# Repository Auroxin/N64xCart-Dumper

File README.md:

# N64xCart Dumper

N64xCart Dumper is a source-available hardware / firmware project for dumping Nintendo 64 cartridges as a USB mass storage device. It is based on the excellent DreamDumper64 project and the `DrmDmp64_mass` firmware, with changes for the N64xCart Dumper hardware.

## Project Status

This repository contains:

- `firmware/N64xCartDumper/` - RP2040 firmware adapted for the N64xCart Dumper board.
- `hardware-v2.1/` - current and recommended KiCad and production files.
- `hardware-v1.1/` - legacy hardware files, retained for reference only.
- `extras/` - extra project files, if any.

The device appears to the computer as a USB mass storage device. The virtual FAT16 disk exposes N64 cartridge data and save data files such as ROM, EEPROM, SRAM and FlashRAM where supported by the firmware.

## Origin and Credits

This project exists because of prior open source work. Please visit and support the original authors:

- DreamDumper64 hardware project by khill25: https://github.com/khill25/Dreamdumper
- `DrmDmp64_mass` firmware by nopjne: https://github.com/nopjne/drmdmp64_mass
- Special thanks to [selunders](https://github.com/selunders/N64xCart-Dumper/tree/read_eeprom) for identifying the hardware v1.1 issues affecting CIC information and EEPROM reading, and for providing a detailed repair proposal that helped guide the updated hardware design.
- TinyUSB USB stack: https://github.com/hathach/tinyusb
- Raspberry Pi Pico / RP2040 SDK ecosystem: https://github.com/raspberrypi/pico-sdk

My changes are focused on adapting the firmware and hardware layout for the N64xCart Dumper board, including the PCB layout, production files, and acrylic enclosure design.

## Hardware

The hardware in this repository was redrawn and laid out for the N64xCart Dumper form factor while following the DreamDumper64 hardware principles.

> [!IMPORTANT]
> **Use hardware v2.1 for all new DIY builds. Do not build hardware v1.1.** Version 1.1 does not support reading CIC chip information from N64 cartridges or reading EEPROM save data. Hardware v2.1 resolves these limitations and is expected to be the final hardware revision. The v1.1 files remain in this repository for historical reference only.

<p align="center">
  
  <br>
  <sub><strong>N64xCart Dumper v2.1 — Rear view</strong></sub>
</p>

Current, recommended hardware files:

- KiCad project: `hardware-v2.1/PCB/N64xCartDumper-v2.1.kicad_pro`
- Schematic: `hardware-v2.1/PCB/N64xCartDumper-v2.1.kicad_sch`
- PCB layout: `hardware-v2.1/PCB/N64xCartDumper-v2.1.kicad_pcb`
- Production archive: `hardware-v2.1/production/N64xCart-Dumper-v2.1-20260813.zip`

Legacy v1.1 files are under `hardware-v1.1/` and are not recommended for manufacturing.

## Firmware

The firmware is based on `DrmDmp64_mass`, a mass storage device firmware for DreamDumper64. It has been modified for the N64xCart Dumper hardware.

Important local changes include:

- USB product strings changed to `N64xCart Dumper`.
- Hardware pin and LED configuration adapted for this board.
- Virtual disk label/product information updated for N64xCart Dumper.
- Project files arranged under `firmware/N64xCartDumper/`.

## Building Firmware

The active firmware build entry is the CMake project in `firmware/N64xCartDumper/`.

Typical build flow:

```sh
cd firmware/N64xCartDumper
mkdir build
cd build
cmake ..
cmake --build .
(optional) put pico in bootloader mode and copy the N64xCartDumper.uf2 to the attached drive.
```

You will need a working Raspberry Pi Pico / RP2040 build environment, including the Pico SDK, CMake, a supported ARM GCC toolchain, and the TinyUSB dependencies used by this project.

Note: the included `Makefile` appears to be inherited from an earlier TinyUSB example layout and may not match the current source file names. Prefer the CMake build unless you intentionally update the Makefile.

## Buying a Finished Unit

I also sell assembled N64xCart Dumper units on AliExpress. Units sold through the product link below use the latest v2.1 hardware. Buying one helps support the time spent on PCB layout, testing, assembly, enclosure design, and continued project maintenance.

- Support Us: [Product Link](https://www.aliexpress.com/item/1005012654363194.html)

Thank you for supporting this project. If you build your own non-commercial unit, improve the design, or find a bug, contributions and feedback are welcome.

## License Notes

The original N64xCart Dumper hardware designs, documentation, and project-specific modifications are licensed for **personal and other non-commercial use only** under the terms in [`LICENSE`](LICENSE). Commercial use—including manufacturing or selling boards, assembled units, kits, or derivative products—is prohibited without prior written permission from the applicable copyright holder.

This non-commercial restriction means the project is source-available, but it is not Open Source Hardware or open-source software under the commonly accepted OSI/OSHWA definitions.

This repository also contains code and design work derived from third-party projects. The project-level license does not replace or restrict third-party rights. Check the original projects, file headers, and bundled license files for the terms that apply to those materials:

- `DrmDmp64_mass`: https://github.com/nopjne/drmdmp64_mass
- DreamDumper64: https://github.com/khill25/Dreamdumper
- TinyUSB license file included at `firmware/N64xCartDumper/external/tinyusb/LICENSE`

Source files inherited from `DrmDmp64_mass` include their original copyright notices and headers. Third-party components remain the property of their respective copyright holders and are governed by their respective terms.

## Disclaimer

This is an independent hobbyist/source-available hardware project. It is not affiliated with or endorsed by Nintendo. Use it only with cartridges and data you legally own and are allowed to back up under your local laws.

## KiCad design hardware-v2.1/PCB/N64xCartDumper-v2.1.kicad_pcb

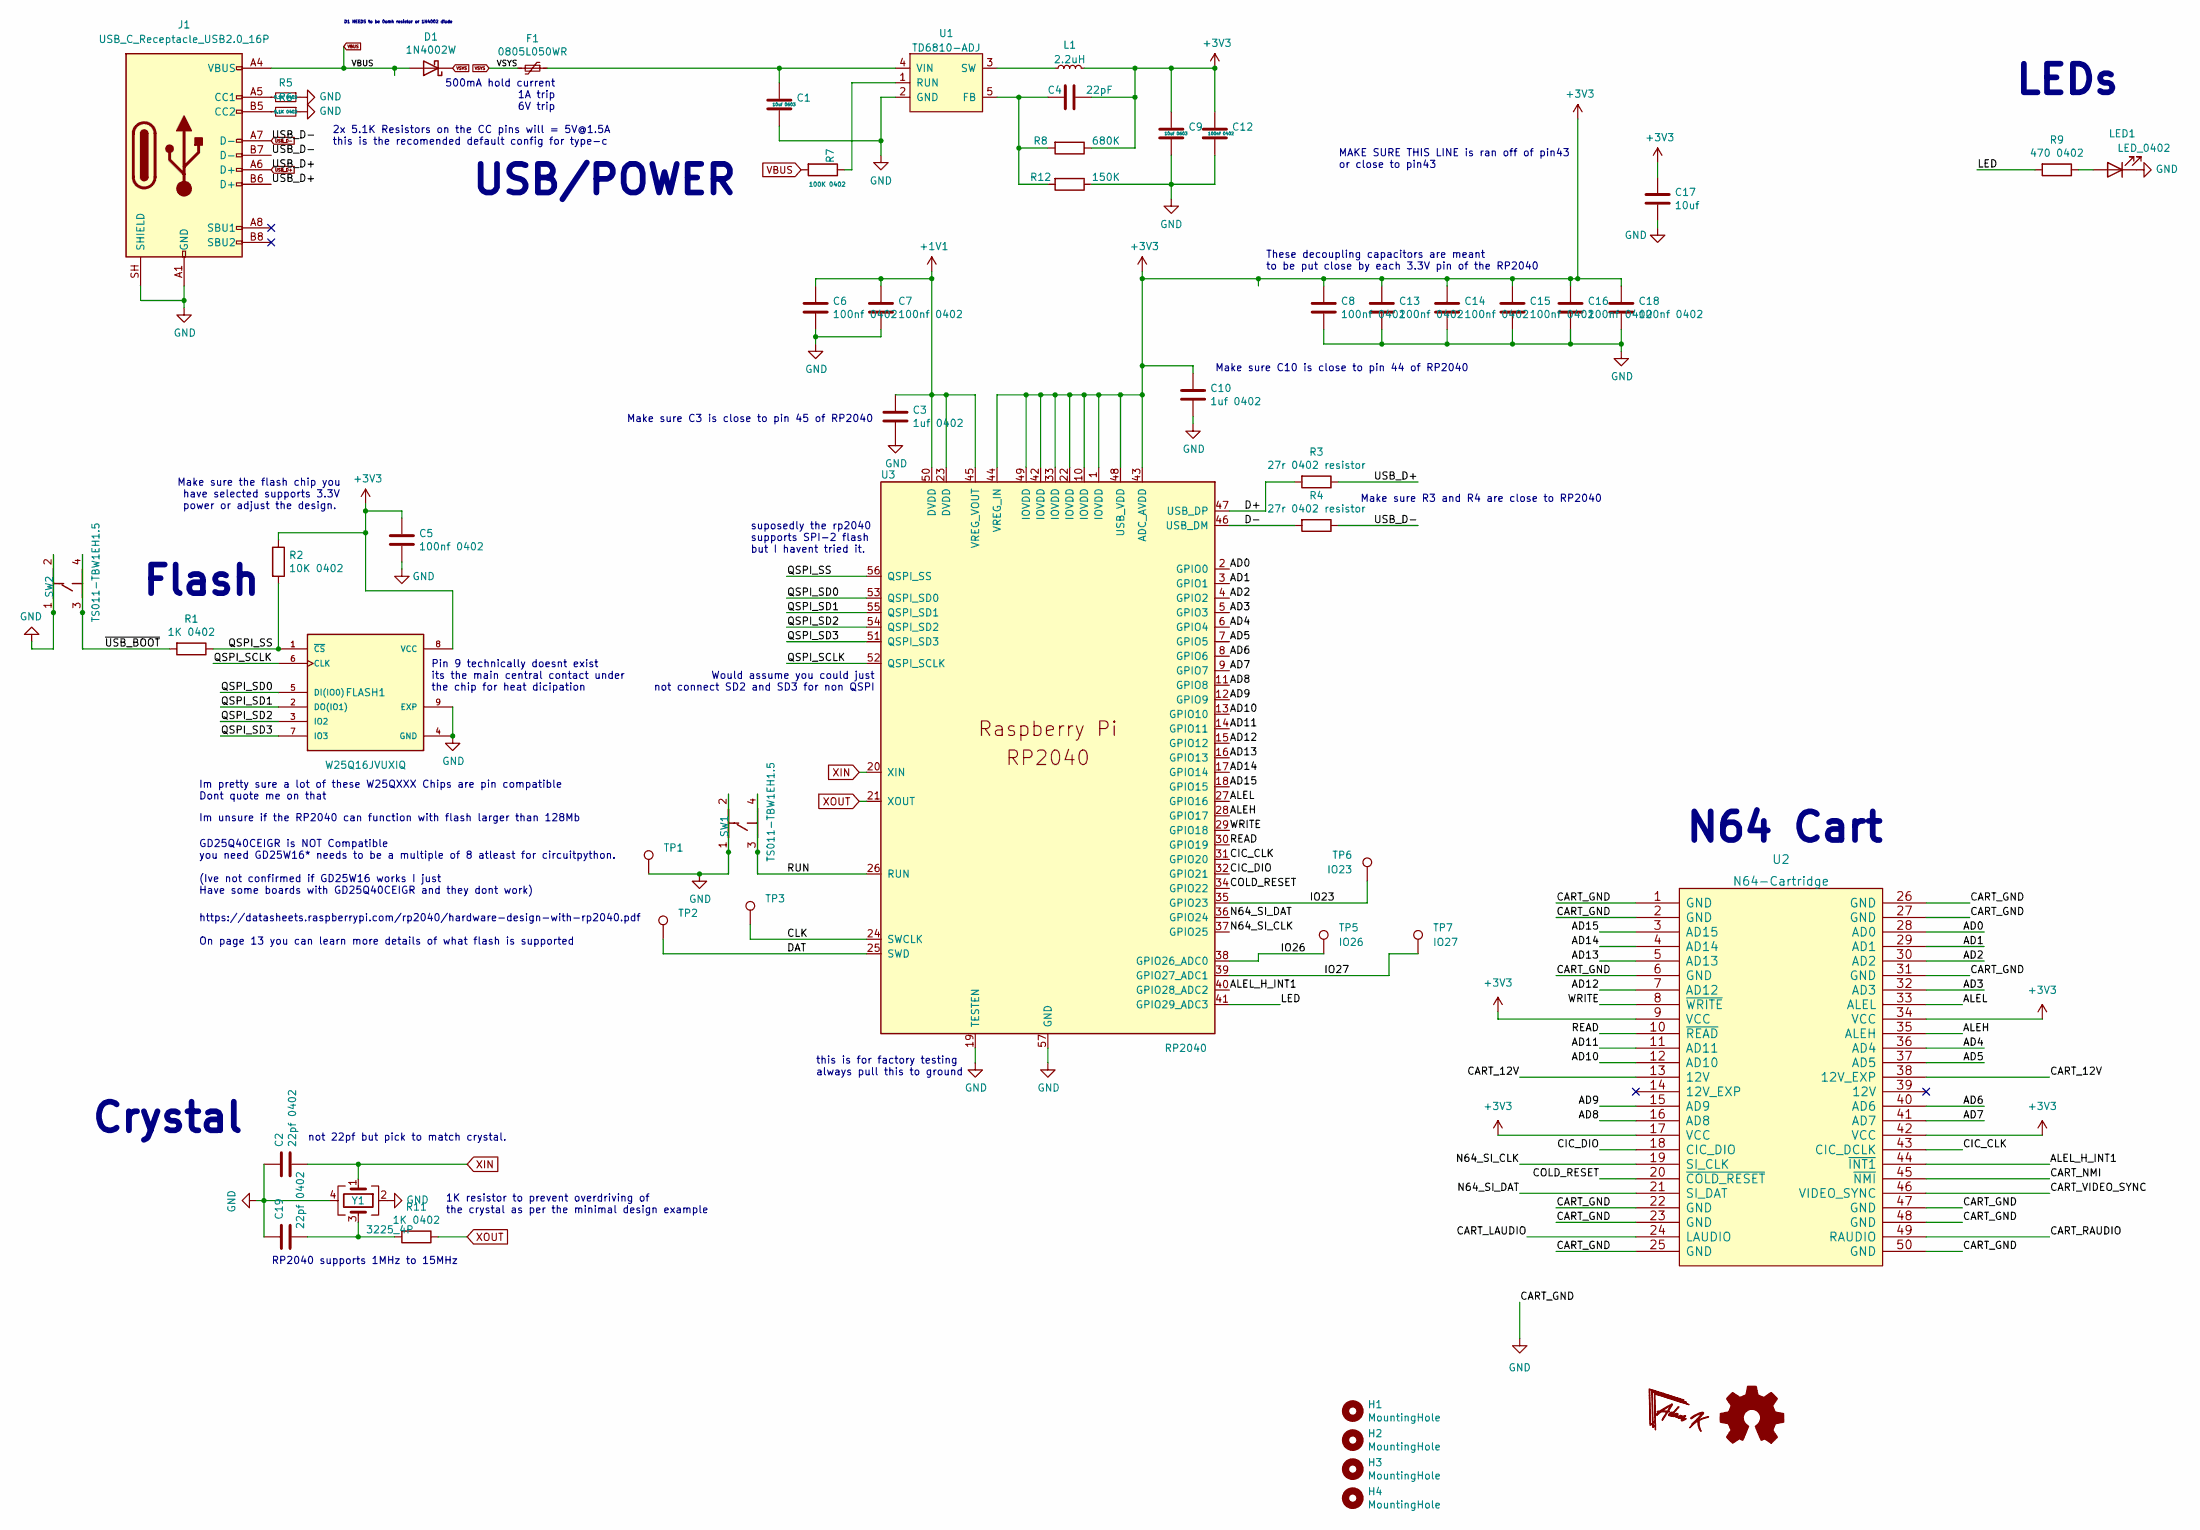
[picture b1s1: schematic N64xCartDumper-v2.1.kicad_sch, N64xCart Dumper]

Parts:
C1, C9: 10uf 0603; C_0603_1608Metric
C2, C19: 22pf 0402; C_0402_1005Metric
C3, C10: 1uf 0402; C_0402_1005Metric
C4: 22pF; C_0402_1005Metric
C5, C6, C7, C8, C12, C13, C14, C15, C16, C18: 100nf 0402; C_0402_1005Metric
C17: 10uf; C_0603_1608Metric
D1: 1N4002W; D_SOD-123
F1: 0805L050WR; Fuse_0805_2012Metric
FLASH1: W25Q16JVUXIQ; Winbond_USON-8-1EP_3x2mm_P0.5mm_EP0.2x1.6mm
H1, H2, H3, H4: MountingHole; MountingHole_3.2mm_M3_Pad
J1: USB_C_Receptacle_USB2.0_16P; USB-C-SMD_SHOU_TYPE-C-16P-CB1.6
L1: 2.2uH; WPN252010UF2R2MT
LED1: LED_0402; LED_0603_1608Metric
R1, R11: 1K 0402; R_0402_1005Metric
R2: 10K 0402; R_0402_1005Metric
R3, R4: 27r 0402 resistor; R_0402_1005Metric
R5, R6: 5.1K 0402; R_0402_1005Metric
R7: 100K 0402; R_0402_1005Metric
R8: 680K; R_0402_1005Metric
R9: 470 0402; R_0402_1005Metric
R12: 150K; R_0402_1005Metric
SW1, SW2: TS011-TBW1EH1.5; SW-SMD_4P-L5.2-W5.2-1; Manufacturer Part TS011-TBW1EH1.5; LCSC Part Name 4*4*1.5mm 立贴 180GF 铜头轻触开关
TP1: GND; TestPoint_Pad_D1.0mm
TP2: DAT; TestPoint_Pad_D1.0mm
TP3: CLK; TestPoint_Pad_D1.0mm
TP5: IO26; TestPoint_Pad_D1.0mm
TP6: IO23; TestPoint_Pad_D1.0mm
TP7: IO27; TestPoint_Pad_D1.0mm
U1: TD6810-ADJ; SOT-23-5
U2: N64-Cartridge; N64-CONN
U3: RP2040; RP2040-QFN-56; LCSC C2040
Y1: 3225_4P; Crystal_SMD_3225-4Pin_3.2x2.5mm

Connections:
+1V1: C3.1, C6.1, C7.1, U3.23 (DVDD), U3.45 (VREG_VOUT), U3.50 (DVDD)
+3V3: C4.2, C5.1, C8.1, C9.1, C10.1, C12.1, C13.1, C14.1, C15.1, C16.1, C17.1, C18.1, FLASH1.8 (VCC), L1.2, R2.1, R8.1, U2.9 (VCC), U2.17 (VCC), U2.34 (VCC), U2.42 (VCC), U3.1 (IOVDD), U3.10 (IOVDD), U3.22 (IOVDD), U3.33 (IOVDD), U3.42 (IOVDD), U3.43 (ADC_AVDD), U3.44 (VREG_IN), U3.48 (USB_VDD), U3.49 (IOVDD)
/AD0: U2.28 (AD0), U3.2 (GPIO0)
/AD1: U2.29 (AD1), U3.3 (GPIO1)
/AD2: U2.30 (AD2), U3.4 (GPIO2)
/AD3: U2.32 (AD3), U3.5 (GPIO3)
/AD4: U2.36 (AD4), U3.6 (GPIO4)
/AD5: U2.37 (AD5), U3.7 (GPIO5)
/AD6: U2.40 (AD6), U3.8 (GPIO6)
/AD7: U2.41 (AD7), U3.9 (GPIO7)
/AD8: U2.16 (AD8), U3.11 (GPIO8)
/AD9: U2.15 (AD9), U3.12 (GPIO9)
/AD10: U2.12 (AD10), U3.13 (GPIO10)
/AD11: U2.11 (AD11), U3.14 (GPIO11)
/AD12: U2.7 (AD12), U3.15 (GPIO12)
/AD13: U2.5 (AD13), U3.16 (GPIO13)
/AD14: U2.4 (AD14), U3.17 (GPIO14)
/AD15: U2.3 (AD15), U3.18 (GPIO15)
/ALEH: U2.35 (ALEH), U3.28 (GPIO17)
/ALEL: U2.33 (ALEL), U3.27 (GPIO16)
/ALEL_H_INT1: U2.44 (~INT1), U3.40 (GPIO28_ADC2)
/CART_12V: U2.13 (12V), U2.38 (12V_EXP)
/CART_LAUDIO: U2.24 (LAUDIO)
/CART_NMI: U2.45 (~NMI)
/CART_RAUDIO: U2.49 (RAUDIO)
/CART_VIDEO_SYNC: U2.46 (VIDEO_SYNC)
/CIC_CLK: U2.43 (CIC_DCLK), U3.31 (GPIO20)
/CIC_DIO: U2.18 (CIC_DIO), U3.32 (GPIO21)
/CLK: TP3.1 (1_1), U3.24 (SWCLK)
/COLD_RESET: U2.20 (~COLD_RESET), U3.34 (GPIO22)
/D+: R3.2, U3.47 (USB_DP)
/D-: R4.2, U3.46 (USB_DM)
/DAT: TP2.1 (1_1), U3.25 (SWD)
/IO23: TP6.1 (1_1), U3.35 (GPIO23)
/IO26: TP5.1 (1_1), U3.38 (GPIO26_ADC0)
/IO27: TP7.1 (1_1), U3.39 (GPIO27_ADC1)
/LED: R9.2, U3.41 (GPIO29_ADC3)
/N64_SI_CLK: U2.19 (SI_CLK), U3.37 (GPIO25)
/N64_SI_DAT: U2.21 (SI_DAT), U3.36 (GPIO24)
/QSPI_SCLK: FLASH1.6 (CLK), U3.52 (QSPI_SCLK)
/QSPI_SD0: FLASH1.5 (DI(IO0)), U3.53 (QSPI_SD0)
/QSPI_SD1: FLASH1.2 (DO(IO1)), U3.55 (QSPI_SD1)
/QSPI_SD2: FLASH1.3 (IO2), U3.54 (QSPI_SD2)
/QSPI_SD3: FLASH1.7 (IO3), U3.51 (QSPI_SD3)
/QSPI_SS: FLASH1.1 (~CS), R1.1, R2.2, U3.56 (QSPI_SS)
/READ: U2.10 (~READ), U3.30 (GPIO19)
/RUN: SW1.3, SW1.4, U3.26 (RUN)
/WRITE: U2.8 (~WRITE), U3.29 (GPIO18)
/~USB_BOOT: R1.2, SW2.3, SW2.4
GND: C1.2, C2.1, C3.2, C5.2, C6.2, C7.2, C8.2, C9.2, C10.2, C12.2, C13.2, C14.2, C15.2, C16.2, C17.2, C18.2, C19.1, FLASH1.4 (GND), FLASH1.9 (EXP), J1.A1 (GND), J1.A12 (GND), J1.B1 (GND), J1.B12 (GND), J1.SH (SHIELD), LED1.1 (K), R5.1, R6.1, R12.1, SW1.1, SW1.2, SW2.1, SW2.2, TP1.1 (1_1), U1.2 (GND), U2.1 (GND), U2.2 (GND), U2.6 (GND), U2.22 (GND), U2.23 (GND), U2.25 (GND), U2.26 (GND), U2.27 (GND), U2.31 (GND), U2.47 (GND), U2.48 (GND), U2.50 (GND), U3.19 (TESTEN), U3.57 (GND), Y1.2, Y1.4
unnamed: C19.2, R11.2, Y1.3
unnamed: J1.A5 (CC1), R5.2
unnamed: J1.B5 (CC2), R6.2
unnamed: LED1.2 (A), R9.1
unnamed: C4.1, R8.2, R12.2, U1.5 (FB)
unnamed: R7.1, U1.1 (RUN)
unnamed: L1.1, U1.3 (SW)
unnamed: C1.1, F1.1, U1.4 (VIN)
USB_D+: J1.A6 (D+), J1.B6 (D+), R3.1
USB_D-: J1.A7 (D-), J1.B7 (D-), R4.1
VBUS: D1.2 (A), J1.A4 (VBUS), J1.A9 (VBUS), J1.B4 (VBUS), J1.B9 (VBUS), R7.2
VSYS: D1.1 (K), F1.2
XIN: C2.2, U3.20 (XIN), Y1.1
XOUT: R11.1, U3.21 (XOUT)

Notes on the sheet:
USB/POWER
GD25Q40CEIGR is NOT Compatible you need GD25W16* needs to be a multiple of 8 atleast for circuitpython. (Ive not confirmed if GD25W16 works I just Have some boards with GD25Q40CEIGR and they dont work)
D1 NEEDS to be 0omh resistor or 1N4002 diode
https://datasheets.raspberrypi.com/rp2040/hardware-design-with-rp2040.pdf On page 13 you can learn more details of what flash is supported
Pin 9 technically doesnt exist its the main central contact under the chip for heat dicipation
Make sure R3 and R4 are close to RP2040
this is for factory testing always pull this to ground
Im unsure if the RP2040 can function with flash larger than 128Mb
Would assume you could just not connect SD2 and SD3 for non QSPI
These decoupling capacitors are meant to be put close by each 3.3V pin of the RP2040
N64 Cart
Flash
Im pretty sure a lot of these W25QXXX Chips are pin compatible Dont quote me on that
not 22pf but pick to match crystal.
2x 5.1K Resistors on the CC pins will = 5V@1.5A this is the recomended default config for type-c
suposedly the rp2040 supports SPI-2 flash but I havent tried it.
1K resistor to prevent overdriving of the crystal as per the minimal design example
LEDs
RP2040 supports 1MHz to 15MHz
Make sure the flash chip you have selected supports 3.3V power or adjust the design.
MAKE SURE THIS LINE is ran off of pin43 or close to pin43
Crystal
500mA hold current 1A trip 6V trip
Make sure C3 is close to pin 45 of RP2040
Make sure C10 is close to pin 44 of RP2040

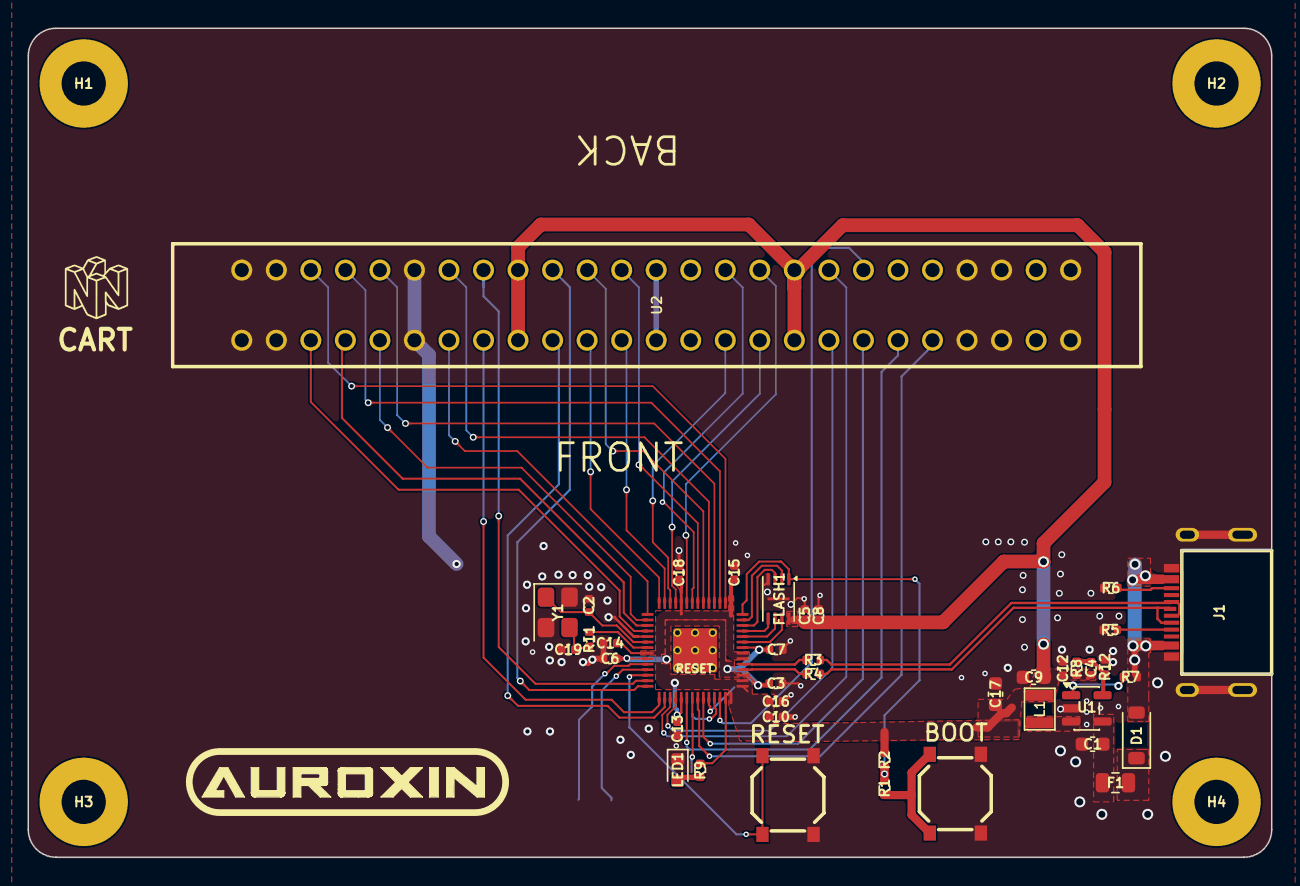
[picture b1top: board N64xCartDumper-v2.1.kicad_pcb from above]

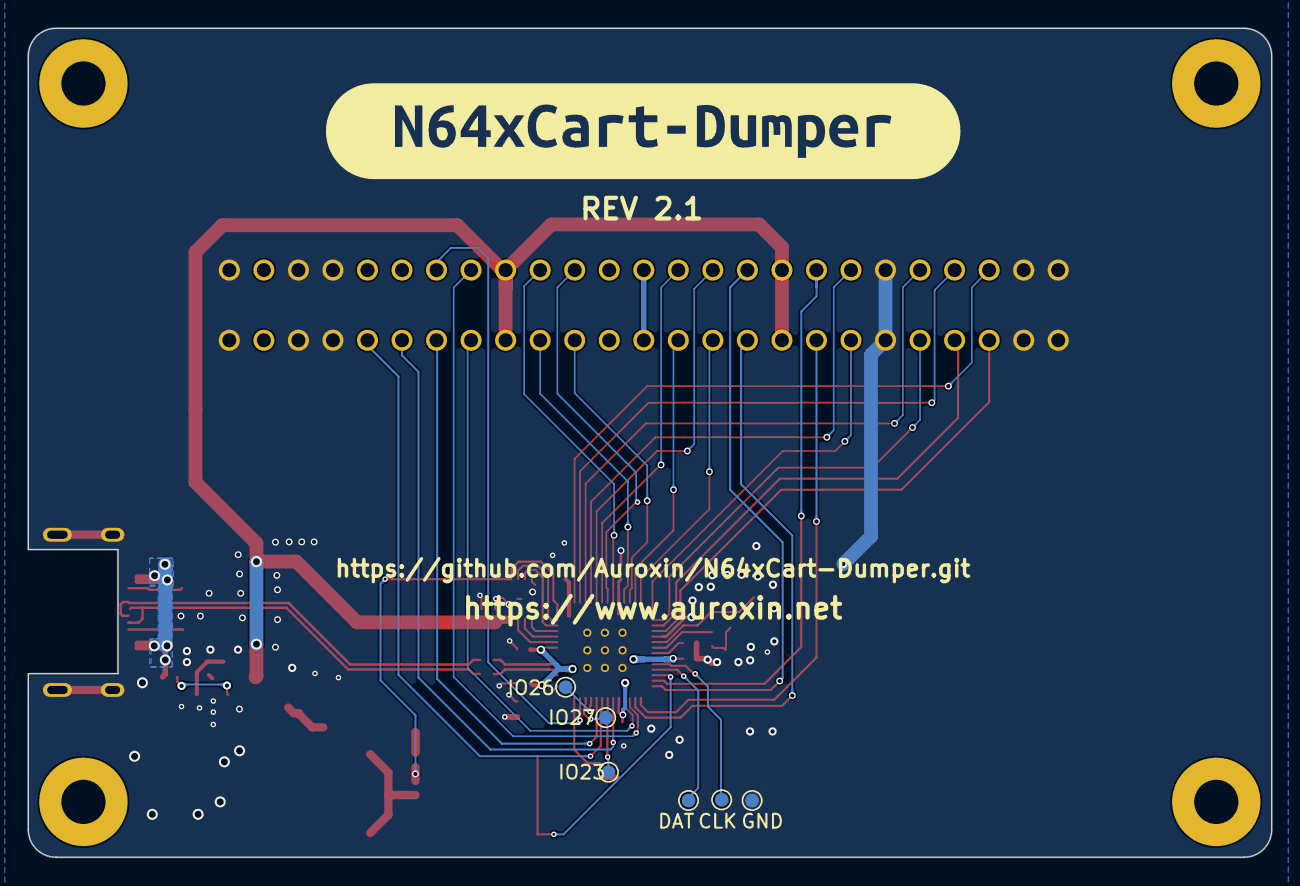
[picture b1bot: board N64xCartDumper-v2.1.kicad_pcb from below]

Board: 2 copper layers, 90.0 x 60.0 mm, 52 parts (7 on the bottom side), 60 nets.

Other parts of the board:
kibuzzard-6A2BC31C: G***; kibuzzard-6A2BC31C
